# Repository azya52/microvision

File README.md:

# microvision
Microvision Homebrew

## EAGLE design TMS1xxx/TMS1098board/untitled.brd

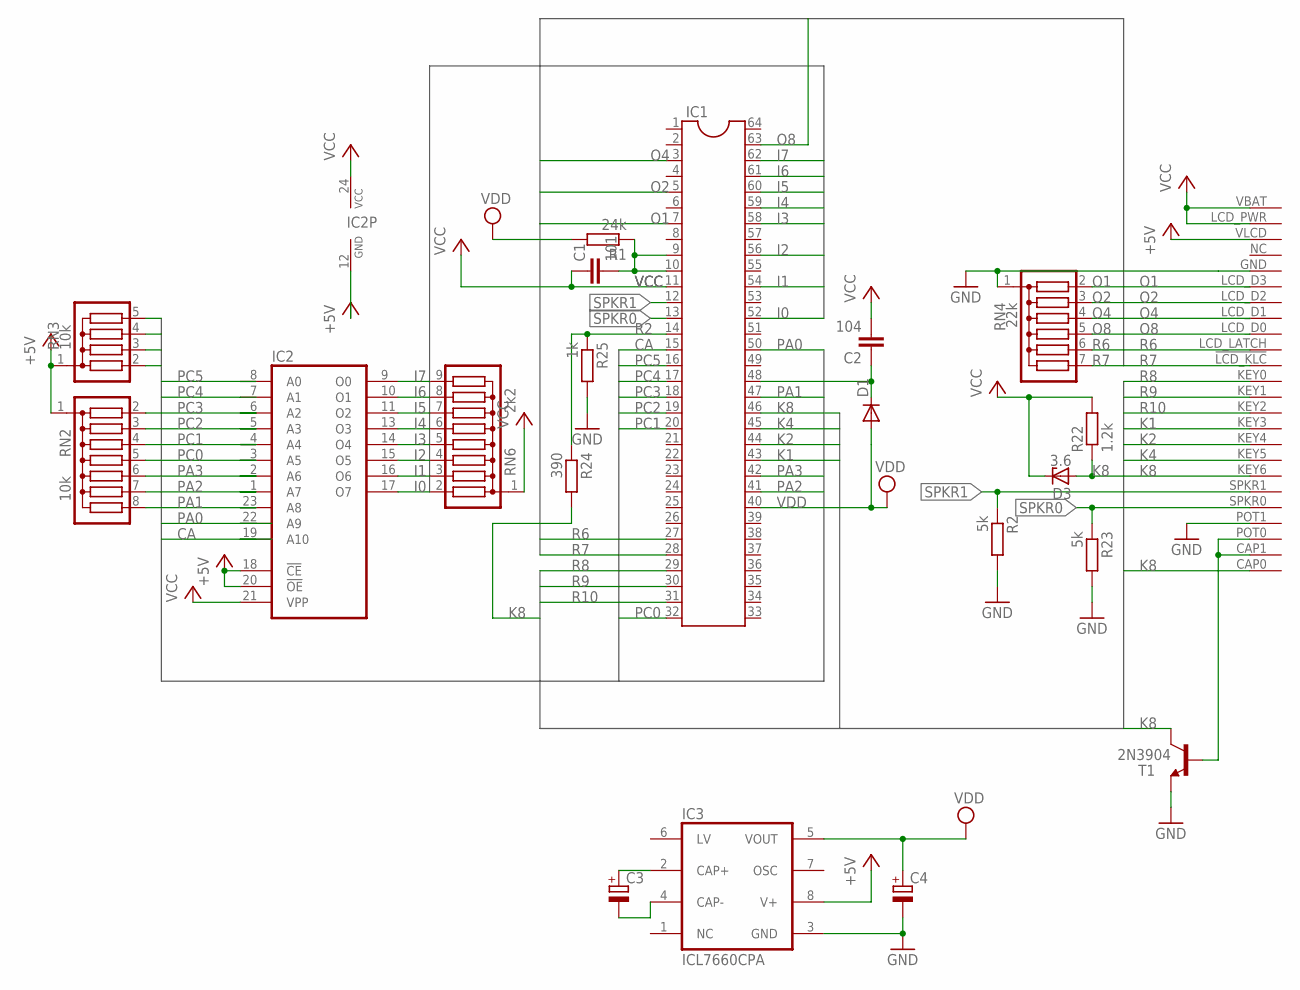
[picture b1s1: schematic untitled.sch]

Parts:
C1: 101; C025-024X044
C2: 104; C025-024X044
C3, C4: CPOL-EUE2.5-5; E2,5-5
D1: DIODE-D-5; D-5
D3: 3.6; ZDIO-7.5
IC1: DIL64
IC2: 2716; DIL24
IC3: ICL7660CPA; DIL08
R1: 24k; 0204/7
R2, R23: 5k; 0204/7
R22: 1.2k; 0204/7
R24: 390; 0207/10
R25: 1k; 0207/10
RN2: 10k; SIL8
RN3: 10k; SIL5
RN4: 22k; SIL7
RN6: 2k2; SIL9
T1: 2N3904; TO92
U$1: CONNECTOR

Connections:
+5V: IC2.12 (GND), IC2.18 (!CE), IC2.20 (!OE), IC3.8 (V+), RN2.1, RN3.1, U$1.VLCD
CA: IC1.15, IC2.19 (A10), RN3.3
GND: C4.-, IC3.3 (GND), R2.2, R23.2, R25.2, RN4.1, T1.3 (E), U$1.GND, U$1.POT1
I0: IC1.52, IC2.17 (O7), RN6.2
I1: IC1.54, IC2.16 (O6), RN6.3
I2: IC1.56, IC2.15 (O5), RN6.4
I3: IC1.58, IC2.14 (O4), RN6.5
I4: IC1.59, IC2.13 (O3), RN6.6
I5: IC1.60, IC2.11 (O2), RN6.7
I6: IC1.61, IC2.10 (O1), RN6.8
I7: IC1.62, IC2.9 (O0), RN6.9
K1: IC1.43, U$1.KEY3
K2: IC1.44, U$1.KEY4
K4: IC1.45, U$1.KEY5
K8: D3.A, IC1.46, R22.1, R24.2, T1.1 (C), U$1.CAP0, U$1.KEY6
unnamed: C2.1, D1.C, IC1.48
unnamed: C1.2, IC1.9, IC1.10, R1.1
unnamed: T1.2 (B), U$1.CAP1, U$1.POT0
unnamed: C3.+, IC3.2 (CAP+)
unnamed: C3.-, IC3.4 (CAP-)
O1: IC1.7, RN4.2, U$1.LCD_D3
O2: IC1.5, RN4.3, U$1.LCD_D2
O4: IC1.3, RN4.4, U$1.LCD_D1
O8: IC1.63, RN4.5, U$1.LCD_D0
PA0: IC1.50, IC2.22 (A9), RN3.2
PA1: IC1.47, IC2.23 (A8), RN2.8
PA2: IC1.41, IC2.1 (A7), RN2.7
PA3: IC1.42, IC2.2 (A6), RN2.6
PC0: IC1.32, IC2.3 (A5), RN2.5
PC1: IC1.20, IC2.4 (A4), RN2.4
PC2: IC1.19, IC2.5 (A3), RN2.3
PC3: IC1.18, IC2.6 (A2), RN2.2
PC4: IC1.17, IC2.7 (A1), RN3.4
PC5: IC1.16, IC2.8 (A0), RN3.5
R2: IC1.14, R24.1, R25.1
R6: IC1.27, RN4.6, U$1.LCD_LATCH
R7: IC1.28, RN4.7, U$1.!LCD_KLC (LCD_CLK)
R8: IC1.29, U$1.KEY0
R9: IC1.30, U$1.KEY1
R10: IC1.31, U$1.KEY2
SPKR0: IC1.13, R23.1, U$1.SPKR0
SPKR1: IC1.12, R2.1, U$1.SPKR1
VCC: C1.1, C2.2, D3.C, IC1.11, IC2.21 (VPP), IC2.24 (VCC), R22.2, RN6.1, U$1.LCD_PWR, U$1.VBAT
VDD: C4.+, D1.A, IC1.40, IC3.5 (VOUT), R1.2

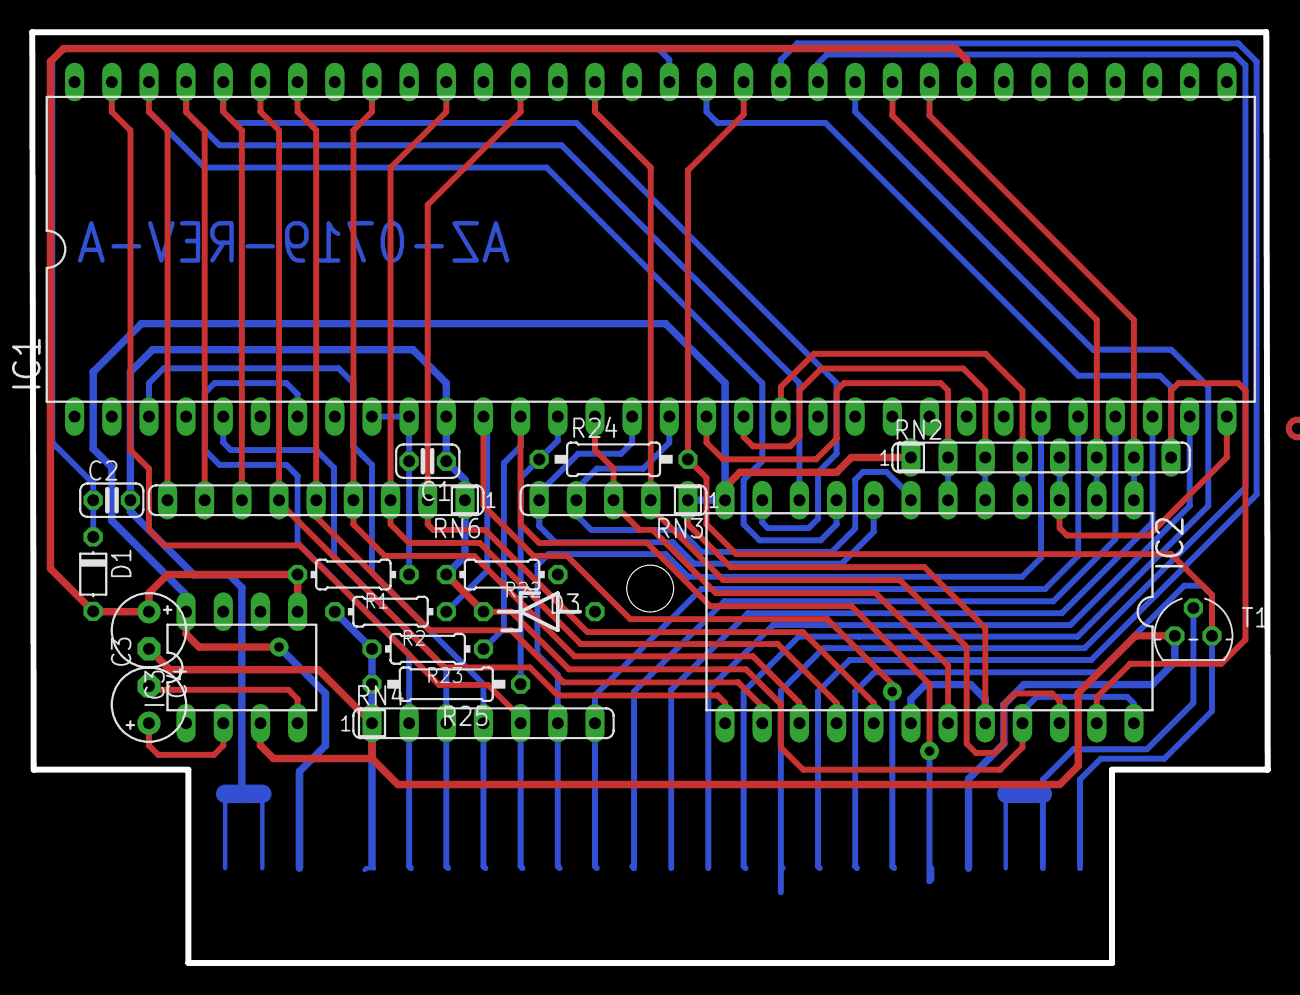
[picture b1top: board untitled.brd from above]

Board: 2 copper layers, 84.4 x 63.6 mm, 21 parts (1 on the bottom side), 44 nets.

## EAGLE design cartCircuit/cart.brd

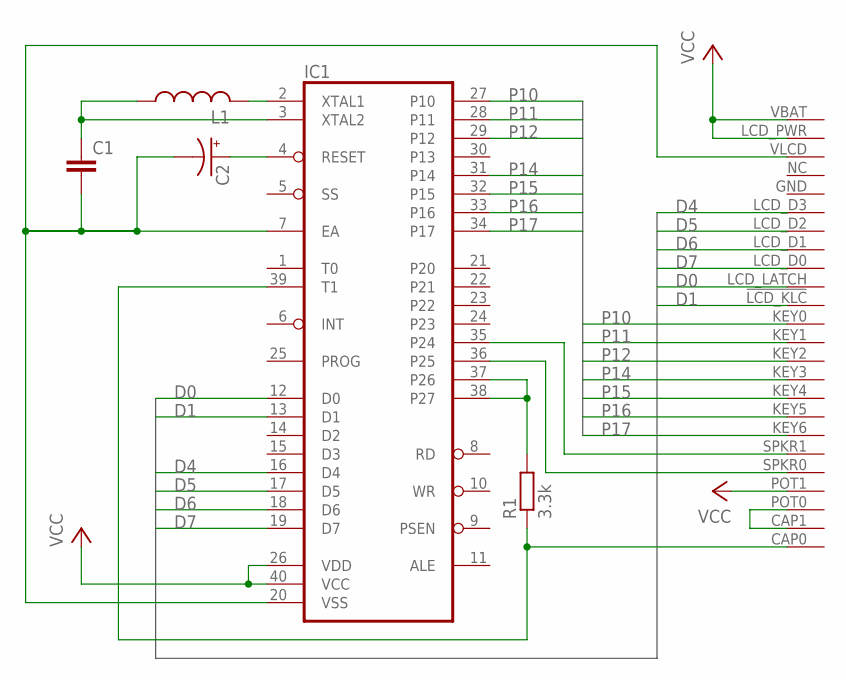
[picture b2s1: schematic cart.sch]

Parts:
C1: C-EU050-024X044; C050-024X044
C2: CPOL-USE2.5-5; E2,5-5
IC1: 8748; DIL40
L1: L-US0207/10; 0207/10
R1: 3.3k; 0204/7
U$1: CONNECTOR

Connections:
D0: IC1.12 (D0), U$1.LCD_LATCH
D1: IC1.13 (D1), U$1.!LCD_KLC (LCD_CLK)
D4: IC1.16 (D4), U$1.LCD_D3
D5: IC1.17 (D5), U$1.LCD_D2
D6: IC1.18 (D6), U$1.LCD_D1
D7: IC1.19 (D7), U$1.LCD_D0
unnamed: IC1.35 (P24), U$1.SPKR1
unnamed: IC1.36 (P25), U$1.SPKR0
unnamed: IC1.37 (P26), IC1.38 (P27), R1.2
unnamed: IC1.39 (T1), R1.1, U$1.CAP0
unnamed: C1.2, C2.-, IC1.7 (EA), IC1.20 (VSS), U$1.VLCD
unnamed: U$1.CAP1, U$1.POT0
unnamed: IC1.2 (XTAL1), L1.2
unnamed: C1.1, IC1.3 (XTAL2), L1.1
unnamed: C2.+, IC1.4 (RESET)
P10: IC1.27 (P10), U$1.KEY0
P11: IC1.28 (P11), U$1.KEY1
P12: IC1.29 (P12), U$1.KEY2
P14: IC1.31 (P14), U$1.KEY3
P15: IC1.32 (P15), U$1.KEY4
P16: IC1.33 (P16), U$1.KEY5
P17: IC1.34 (P17), U$1.KEY6
VCC: IC1.26 (VDD), IC1.40 (VCC), U$1.LCD_PWR, U$1.POT1, U$1.VBAT

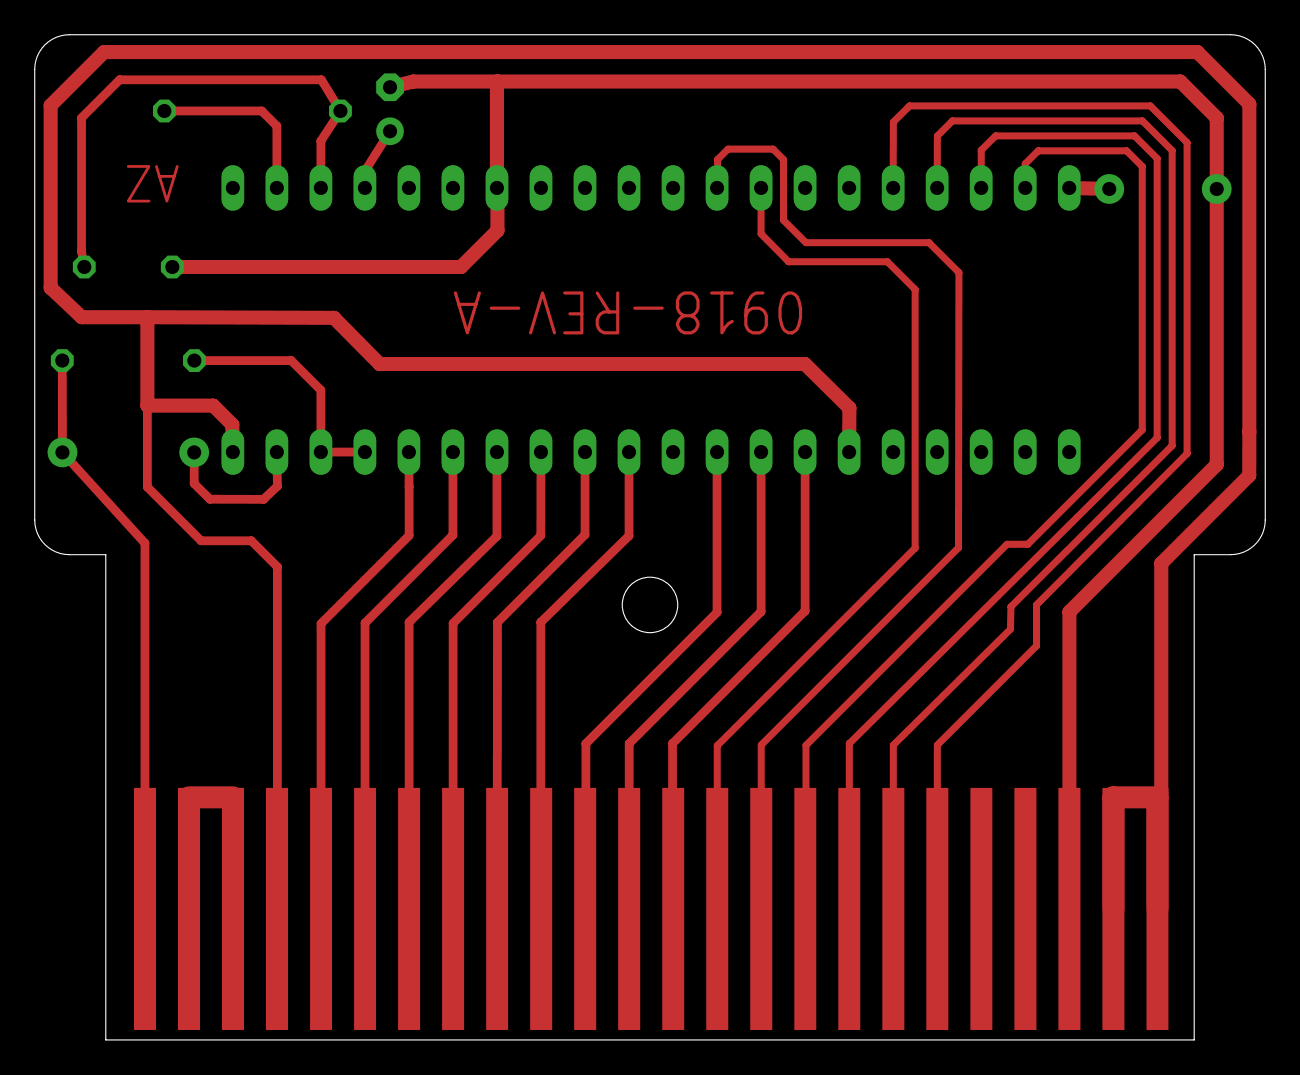
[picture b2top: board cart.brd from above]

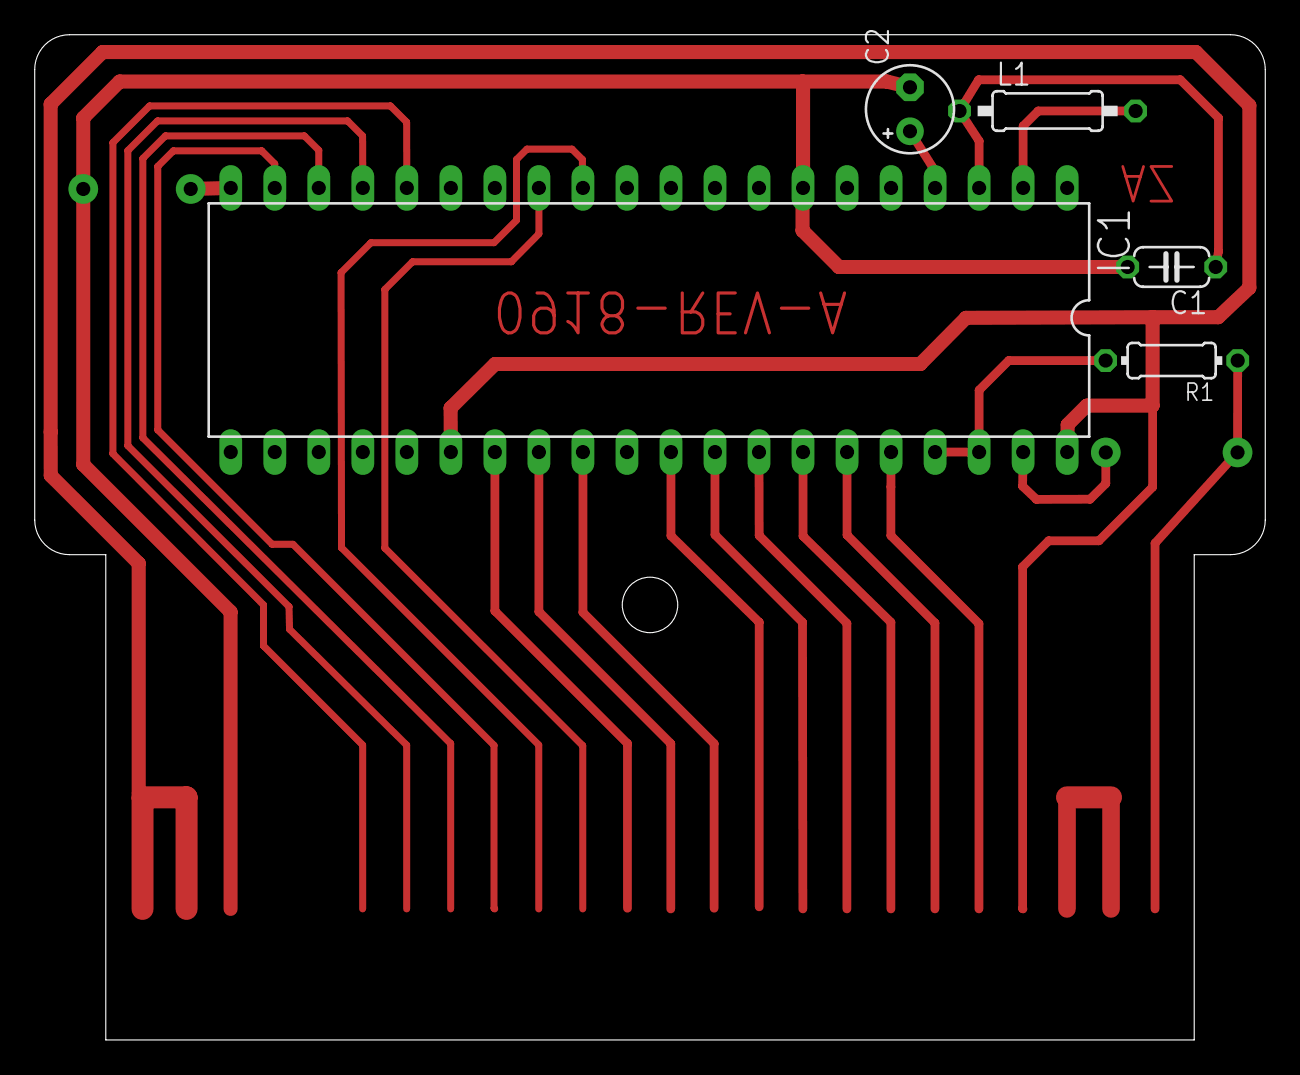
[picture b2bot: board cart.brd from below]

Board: 2 copper layers, 71.0 x 58.0 mm, 6 parts (5 on the bottom side), 23 nets.

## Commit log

2019-02-26 add TMS1xxx
2019-02-27 add mvem with tetris
2024-04-11 del MVEMwithTetris.zip
